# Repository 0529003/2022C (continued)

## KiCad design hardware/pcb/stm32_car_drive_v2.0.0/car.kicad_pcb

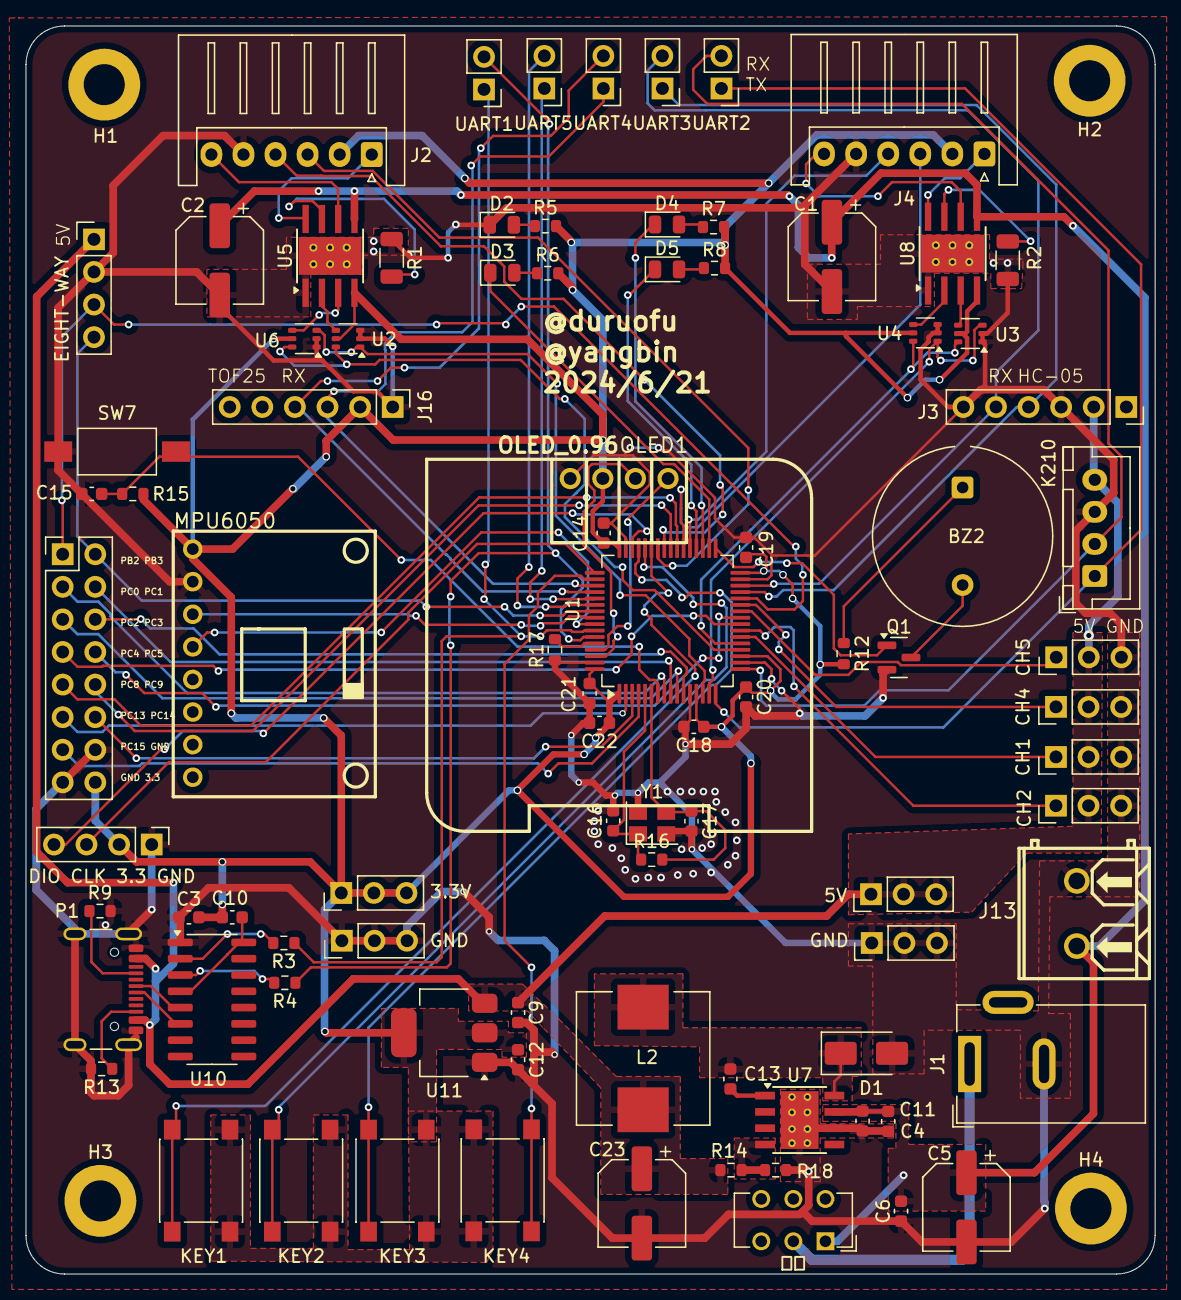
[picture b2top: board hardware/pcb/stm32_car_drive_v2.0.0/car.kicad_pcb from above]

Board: 2 copper layers, 88.0 x 97.3 mm, 92 parts (0 on the bottom side), 84 nets.

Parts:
3.3V, 5V: Conn_01x03; PinHeader_1x03_P2.54mm_Vertical
BZ2: Buzzer; Indicator_PUI_AI-1440-TWT-24V-2-R
C1, C2: 100uf; CP_Elec_6.3x7.7
C3: 0.1uF; C_0603_1608Metric
C4, C11: 4.7uf; C_0603_1608Metric
C5, C23: 220uf; CP_Elec_6.3x7.7
C6, C10: 0.1uf; C_0603_1608Metric
C9, C12: 2.2uF; C_0603_1608Metric
C13: 0.01uf; C_0603_1608Metric
C14, C18, C19, C20, C21, C22: 0.1uf/16V; C_0603_1608Metric
C15: 0.1uF/50V; C_0603_1608Metric
C16, C17: 22pf/16V; C_0603_1608Metric
CH1, CH2, CH4, CH5: Conn_01x03; PinHeader_1x03_P2.54mm_Vertical
D1: B340; D_SMA
D2, D3, D4, D5: LED; LED_0805_2012Metric
DIO CLK 3.3 GND: Conn_01x04; PinHeader_1x04_P2.54mm_Vertical
EIGHT-WAY: Conn_01x04; PinHeader_1x04_P2.54mm_Vertical
GND: Conn_01x03; PinHeader_1x03_P2.54mm_Vertical
GND#2: Conn_01x03; PinHeader_1x03_P2.54mm_Vertical
H1, H2, H3, H4: MountingHole; MountingHole_3.2mm_M3_DIN965_Pad
J1: DC母座(大)
J2, J4: Conn_01x06; JST_XH_S6B-XH-A_1x06_P2.50mm_Horizontal
J3: HC-05; PinSocket_1x06_P2.54mm_Vertical
J13: Conn_01x02; CONN-TH_2P-P5.08
J16: HC-05; PinHeader_1x06_P2.54mm_Vertical
K210: Conn_01x04; JST_XH_B4B-XH-A_1x04_P2.50mm_Vertical
KEY1: K1; SW_Push_1P1T_NO_6x6mm
KEY2: K2; SW_Push_1P1T_NO_6x6mm
KEY3: K3; SW_Push_1P1T_NO_6x6mm
KEY4: K4; SW_Push_1P1T_NO_6x6mm
L2: 22uh; L_Wuerth_HCI-1040
MPU6050: Conn_01x08; MPU6050-GY-521
OLED1: OLED_0.96; 0.96OLED_4P
P1: USB_C_Plug_USB2.0; USB_C_Receptacle_GCT_USB4105-xx-A_16P_TopMnt_Horizontal
PB2 PB3: Conn_02x08_Counter_Clockwise; PinHeader_2x08_P2.54mm_Vertical
Q1: S8050; SOT-23
R1, R2: 0.15R 1206 1WOCP=3.3V/10/0.15R=2.2A; R_1206_3216Metric
R3, R4: 0; R_0603_1608Metric
R5, R6, R7, R8, R17: 10k; R_0603_1608Metric
R9, R13: 5.1K; R_0603_1608Metric
R12: 20; R_0603_1608Metric
R14: R; R_0603_1608Metric
R15: 10K; R_0603_1608Metric
R16: 1M; R_0603_1608Metric
R18: 3.2k; R_0603_1608Metric
SW7: RST; SW_SPST_FSMSM
U1: STM32F103RCTx; LQFP-64_10x10mm_P0.5mm
U2, U3, U4, U6: SOT-363_SC-70-6
U5, U8: DRV8870DDA; Texas_HTSOP-8-1EP_3.9x4.9mm_P1.27mm_EP2.95x4.9mm_Mask2.4x3.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
U7: TPS5430DDA; TI_SO-PowerPAD-8_ThermalVias
U10: CH340C; SOIC-16_3.9x9.9mm_P1.27mm
U11: SGM2212-3.3XKC3G/TR; SOT-223
UART1, UART2, UART3, UART4, UART5: Conn_01x02; PinHeader_1x02_P2.54mm_Vertical
Y1: Crystal_GND24(8M); Crystal_SMD_3225-4Pin_3.2x2.5mm
电源: SW_Push_SPDT; SW_CuK_JS202011CQN_DPDT_Straight

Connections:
+3.3V: 3.3V.1, 3.3V.2, 3.3V.3, C3.2, C10.2, C12.1, C14.1, C18.1, C19.1, C20.1, C21.1, C22.1, DIO CLK 3.3 GND.2, J2.2, J4.2, J16.2, KEY1.2, KEY2.2, KEY3.2, KEY4.2, MPU6050.1, OLED1.2 (VCC), PB2 PB3.16, R5.2, R6.2, R7.2, R8.2, R12.2, R15.2, U1.1 (VBAT), U1.13 (VDDA), U1.19 (VDD), U1.32 (VDD), U1.48 (VDD), U1.64 (VDD), U2.5, U3.5, U4.5, U5.4 (VREF), U6.5, U8.4 (VREF), U11.2 (VOUT), U11.4 (VOUT)
+5V: 5V.1, 5V.2, 5V.3, C9.1, C23.1, CH1.2, CH2.2, CH4.2, CH5.2, EIGHT-WAY.1, J3.2, K210.4, L2.2, P1.A4 (VBUS), P1.A9 (VBUS), P1.B4 (VBUS), P1.B9 (VBUS), R14.1, U11.3 (VIN)
+12V: C1.1, C2.1, C4.2, C5.1, C6.2, C11.2, J13.1, U5.5 (VM), U7.7 (VIN), U8.5 (VM), 电源.1 (A)
/-PB2: EIGHT-WAY.3, PB2 PB3.1, U1.28 (PB2)
/-PB3: EIGHT-WAY.4, PB2 PB3.2, U1.55 (PB3)
/-PC0: PB2 PB3.3, U1.8 (PC0)
/-PC1: PB2 PB3.4, U1.9 (PC1)
/-PC2: PB2 PB3.5, U1.10 (PC2)
/-PC3: PB2 PB3.6, U1.11 (PC3)
/-PC4: PB2 PB3.7, U1.24 (PC4)
/-PC5: PB2 PB3.8, U1.25 (PC5)
/-PC8: PB2 PB3.9, U1.39 (PC8)
/-PC9: PB2 PB3.10, U1.40 (PC9)
/-PC13: PB2 PB3.11, U1.2 (PC13)
/-PC14: PB2 PB3.12, U1.3 (PC14)
/-PC15: PB2 PB3.13, U1.4 (PC15)
/Buzzer: Q1.1 (B), U1.33 (PB12)
/DIRA: U1.20 (PA4), U2.6, U6.6
/DIRB: U1.21 (PA5), U3.6, U4.6
/KEY1: KEY1.1, U1.43 (PA10)
/KEY2: KEY2.1, U1.44 (PA11)
/KEY3: KEY3.1, U1.45 (PA12)
/KEY4: KEY4.1, U1.50 (PA15)
/LED1: D3.1 (K), U1.34 (PB13)
/LED2: D4.1 (K), U1.35 (PB14)
/LED3: D5.1 (K), U1.36 (PB15)
/MPU_SCL: MPU6050.3, U1.56 (PB4)
/MPU_SDA: MPU6050.4, U1.57 (PB5)
/OLED_ACL: OLED1.3 (SCL), U1.62 (PB9)
/OLED_SDA: OLED1.4 (SDA), U1.61 (PB8)
/TIM1_CH1: J2.4, U1.41 (PA8)
/TIM1_CH2: J2.3, U1.42 (PA9)
/TIM2_CH1: U1.14 (PA0), U2.1, U6.3
/TIM2_CH2: U1.15 (PA1), U3.3, U4.1
/TIM3_CH1: CH1.1, U1.22 (PA6)
/TIM3_CH2: CH2.1, U1.23 (PA7)
/TIM3_CH3: CH5.1, U1.26 (PB0)
/TIM3_CH4: CH4.1, U1.27 (PB1)
/TIM8_CH1: J4.4, U1.37 (PC6)
/TIM8_CH2: J4.3, U1.38 (PC7)
/USART1_RX: R4.1, U1.59 (PB7), UART1.2
/USART1_TX: R3.1, U1.58 (PB6), UART1.1
/USART2_RX: K210.2, U1.17 (PA3), UART2.2
/USART2_TX: K210.1, U1.16 (PA2), UART2.1
/USART3_RX: J3.5, U1.30 (PB11), UART3.2
/USART3_TX: J3.4, U1.29 (PB10), UART3.1
/USART4_RX: J16.4, U1.52 (PC11), UART4.2
/USART4_TX: J16.3, U1.51 (PC10), UART4.1
/USART5_RX: U1.54 (PD2), UART5.2
/USART5_TX: U1.53 (PC12), UART5.1
/bb68942b/AOUT1: J2.6, U5.6 (OUT1)
/bb68942b/AOUT2: J2.1, U5.8 (OUT2)
/bb68942b/BOUT1: J4.6, U8.6 (OUT1)
/bb68942b/BOUT2: J4.1, U8.8 (OUT2)
/stm32f103rct6/BOOT0: R17.2, U1.60 (BOOT0)
/stm32f103rct6/OSC_IN: C16.1, R16.1, U1.5 (PD0), Y1.1
/stm32f103rct6/OSC_OUT: C17.1, R16.2, U1.6 (PD1), Y1.3
/stm32f103rct6/RST: C15.2, R15.1, SW7.2, U1.7 (NRST)
/stm32f103rct6/SWCLK: DIO CLK 3.3 GND.3, U1.49 (PA14)
/stm32f103rct6/SWDIO: DIO CLK 3.3 GND.4, U1.46 (PA13)
GND: C1.2, C2.2, C3.1, C4.1, C5.2, C6.1, C9.2, C11.1, C12.2, C14.2, C15.1, C16.2, C17.2, C18.2, C19.2, C20.2, C21.2, C22.2, C23.2, CH1.3, CH2.3, CH4.3, CH5.3, D1.2 (A), D2.1 (K), DIO CLK 3.3 GND.1, EIGHT-WAY.2, GND.1, GND.2, GND.3, GND#2.1, GND#2.2, GND#2.3, J1.2, J2.5, J3.3, J3.6, J4.5, J13.2, J16.1, K210.3, MPU6050.2, OLED1.1 (GND), P1.A1 (GND), P1.A12 (GND), P1.B1 (GND), P1.B12 (GND), P1.S1 (SHIELD), PB2 PB3.14, PB2 PB3.15, Q1.2 (E), R1.1, R2.1, R9.2, R13.2, R17.1, R18.2, SW7.1, U1.12 (VSSA), U1.18 (VSS), U1.31 (VSS), U1.47 (VSS), U1.63 (VSS), U2.2, U2.3, U3.1, U3.2, U4.2, U4.3, U5.1 (GND), U5.9 (GND), U6.1, U6.2, U7.6 (GND), U7.9 (GNDPAD), U8.1 (GND), U8.9 (GND), U10.1 (GND), U11.1 (GND), Y1.2, Y1.4
unnamed: BZ2.2 (+), Q1.3 (C)
unnamed: BZ2.1 (-), R12.1
unnamed: C13.2, D1.1 (K), L2.1, U7.8 (PH)
unnamed: D2.2 (A), R5.1
unnamed: D3.2 (A), R6.1
unnamed: D4.2 (A), R7.1
unnamed: D5.2 (A), R8.1
unnamed: P1.A5 (CC), R9.1
unnamed: P1.A6 (D+), U10.5 (UD+)
unnamed: P1.A7 (D-), U10.6 (UD-)
unnamed: P1.B5 (VCONN), R13.1
unnamed: J1.1, 电源.2 (B)
unnamed: U5.3 (IN1), U6.4
unnamed: U2.4, U5.2 (IN2)
unnamed: R1.2, U5.7 (ISEN)
unnamed: C13.1, U7.1 (BOOT)
unnamed: R14.2, R18.1, U7.4 (VSENSE)
unnamed: U3.4, U8.3 (IN1)
unnamed: U4.4, U8.2 (IN2)
unnamed: R2.2, U8.7 (ISEN)
unnamed: R4.2, U10.3 (RXD)
unnamed: R3.2, U10.2 (TXD)
unnamed: C10.1, U10.4 (V3), U10.16 (VCC)

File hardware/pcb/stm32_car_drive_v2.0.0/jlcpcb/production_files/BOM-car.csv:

Comment,Designator,Footprint,LCSC
Conn_01x02,UART2,PinHeader_1x02_P2.54mm_Vertical,
0.1uf/16V,C19,C_0603_1608Metric,
TPS5430DDA,U7,TI_SO-PowerPAD-8_ThermalVias,
Conn_01x06,J4,JST_XH_S6B-XH-A_1x06_P2.50mm_Horizontal,
~,U6,SOT-363_SC-70-6,
Conn_01x03,CH4,PinHeader_1x03_P2.54mm_Vertical,
SGM2212-3.3XKC3G/TR,U11,SOT-223,
Conn_01x03,CH2,PinHeader_1x03_P2.54mm_Vertical,
Conn_01x02,UART5,PinHeader_1x02_P2.54mm_Vertical,
Conn_02x08_Counter_Clockwise,PB2 PB3,PinHeader_2x08_P2.54mm_Vertical,
DC母座(大),J1,DC母座(大),
Conn_01x02,UART1,PinHeader_1x02_P2.54mm_Vertical,
~,U3,SOT-363_SC-70-6,
220uf,C5,CP_Elec_6.3x7.7,
0.1uF/50V,C15,C_0603_1608Metric,
USB_C_Plug_USB2.0,P1,USB_C_Receptacle_GCT_USB4105-xx-A_16P_TopMnt_Horizontal,
10k,R7,R_0603_1608Metric,
0.15R 1206 1WOCP=3.3V/10/0.15R=2.2A,R1,R_1206_3216Metric,
RST,SW7,SW_SPST_FSMSM,
3.2k,R18,R_0603_1608Metric,
0.1uF,C3,C_0603_1608Metric,
22pf/16V,C16,C_0603_1608Metric,
5.1K,R9,R_0603_1608Metric,
0.1uf/16V,C20,C_0603_1608Metric,
10k,R6,R_0603_1608Metric,
0.1uf/16V,C18,C_0603_1608Metric,
K3,KEY3,SW_Push_1P1T_NO_6x6mm,
10k,R17,R_0603_1608Metric,
0.01uf,C13,C_0603_1608Metric,
Buzzer,BZ2,Indicator_PUI_AI-1440-TWT-24V-2-R,
22uh,L2,L_Wuerth_HCI-1040,
LED,D5,LED_0805_2012Metric,
0.15R 1206 1WOCP=3.3V/10/0.15R=2.2A,R2,R_1206_3216Metric,
2.2uF,C9,C_0603_1608Metric,
HC-05,J3,PinSocket_1x06_P2.54mm_Vertical,
K1,KEY1,SW_Push_1P1T_NO_6x6mm,
20,R12,R_0603_1608Metric,
4.7uf,C11,C_0603_1608Metric,
LED,D2,LED_0805_2012Metric,
10k,R5,R_0603_1608Metric,
220uf,C23,CP_Elec_6.3x7.7,
DRV8870DDA,U8,Texas_HTSOP-8-1EP_3.9x4.9mm_P1.27mm_EP2.95x4.9mm_Mask2.4x3.1mm_ThermalVias,
4.7uf,C4,C_0603_1608Metric,
100uf,C1,CP_Elec_6.3x7.7,
OLED_0.96,OLED1,0.96OLED_4P,
Conn_01x03,CH1,PinHeader_1x03_P2.54mm_Vertical,
DRV8870DDA,U5,Texas_HTSOP-8-1EP_3.9x4.9mm_P1.27mm_EP2.95x4.9mm_Mask2.4x3.1mm_ThermalVias,
Crystal_GND24(8M),Y1,Crystal_SMD_3225-4Pin_3.2x2.5mm,
~,U2,SOT-363_SC-70-6,
0,R3,R_0603_1608Metric,
22pf/16V,C17,C_0603_1608Metric,
R,R14,R_0603_1608Metric,
Conn_01x03,CH5,PinHeader_1x03_P2.54mm_Vertical,
10k,R8,R_0603_1608Metric,
2.2uF,C12,C_0603_1608Metric,
K4,KEY4,SW_Push_1P1T_NO_6x6mm,
HC-05,J16,PinHeader_1x06_P2.54mm_Vertical,
Conn_01x02,J13,CONN-TH_2P-P5.08,
LED,D4,LED_0805_2012Metric,
0.1uf/16V,C21,C_0603_1608Metric,
STM32F103RCTx,U1,LQFP-64_10x10mm_P0.5mm,
0.1uf,C10,C_0603_1608Metric,
0,R4,R_0603_1608Metric,
0.1uf,C6,C_0603_1608Metric,
Conn_01x04,K210,JST_XH_B4B-XH-A_1x04_P2.50mm_Vertical,
B340,D1,D_SMA,
K2,KEY2,SW_Push_1P1T_NO_6x6mm,
LED,D3,LED_0805_2012Metric,
CH340C,U10,SOIC-16_3.9x9.9mm_P1.27mm,
1M,R16,R_0603_1608Metric,
Conn_01x08,MPU6050,MPU6050-GY-521,
Conn_01x02,UART4,PinHeader_1x02_P2.54mm_Vertical,
5.1K,R13,R_0603_1608Metric,
100uf,C2,CP_Elec_6.3x7.7,
~,U4,SOT-363_SC-70-6,
Conn_01x06,J2,JST_XH_S6B-XH-A_1x06_P2.50mm_Horizontal,
0.1uf/16V,C14,C_0603_1608Metric,
0.1uf/16V,C22,C_0603_1608Metric,
10K,R15,R_0603_1608Metric,
S8050,Q1,SOT-23,
Conn_01x02,UART3,PinHeader_1x02_P2.54mm_Vertical,

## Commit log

2024-07-27 updata
